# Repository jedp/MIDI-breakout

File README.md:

# MIDI Breakout Board

MIDI IN/OUT. 3V3 logic.

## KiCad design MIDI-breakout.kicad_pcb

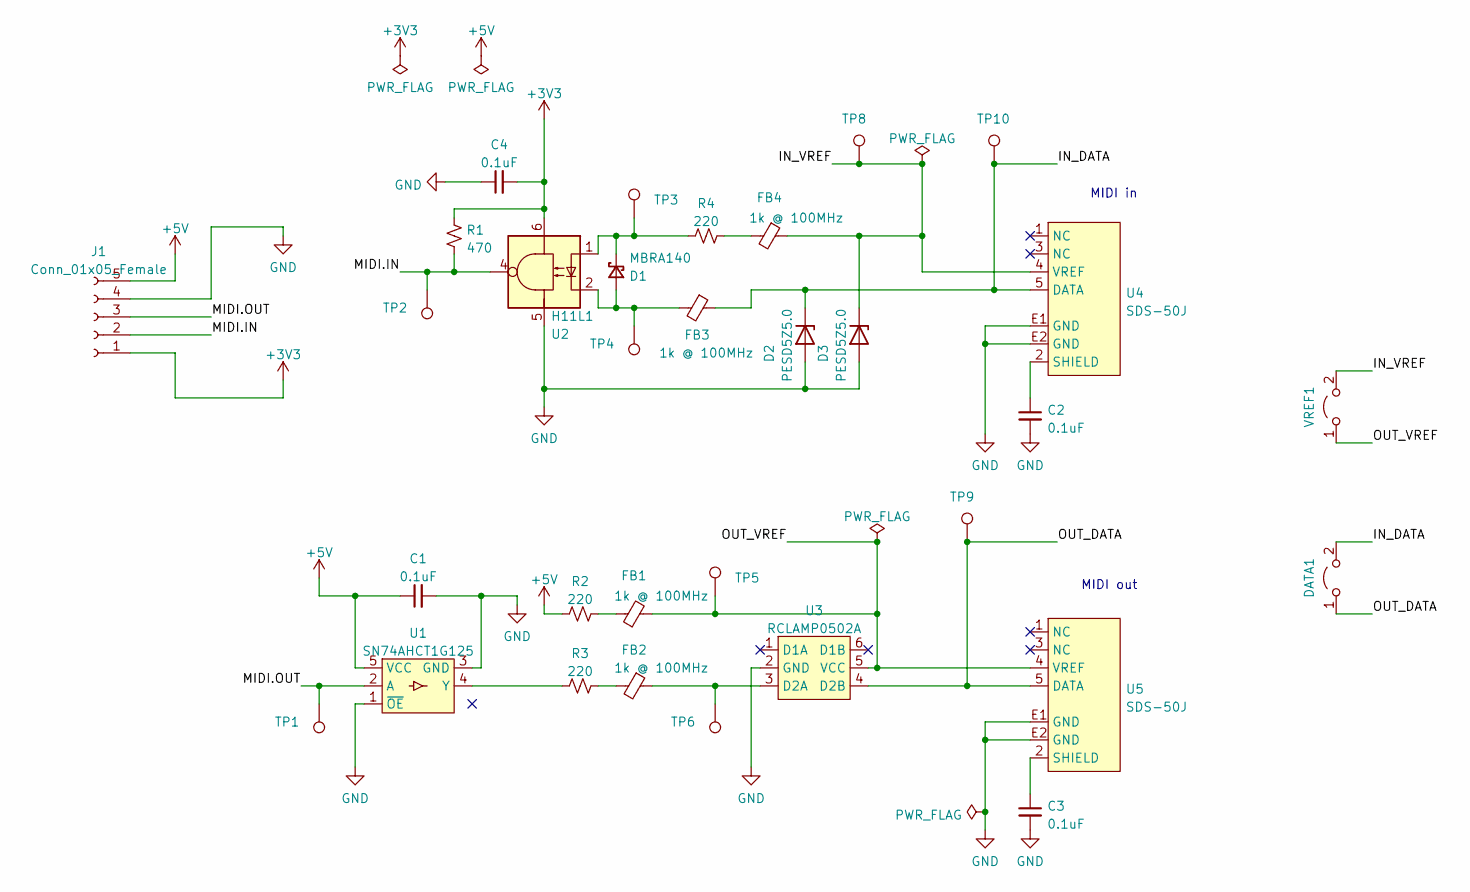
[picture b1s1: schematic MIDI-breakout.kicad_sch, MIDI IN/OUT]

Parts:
C1, C2, C3, C4: 0.1uF; C_0603_1608Metric
D1: MBRA140; DO-214AC (SMA)
D2, D3: PESD5Z5.0; D_SOD-523
DATA1: Jumper_2_Open; PinHeader_1x02_P2.54mm_Vertical
FB1, FB2, FB3, FB4: 1k @ 100MHz; L_0603_1608Metric
J1: Conn_01x05_Female; PinSocket_1x05_P2.54mm_Vertical
R1: 470; R_0603_1608Metric
R2, R3, R4: 220; R_0603_1608Metric
TP1, TP2, TP3, TP4, TP5, TP6, TP8, TP9, TP10: TestPoint; TestPoint_Pad_D1.0mm
U1: SN74AHCT1G125; SOT-23-5
U2: H11L1; DIP-6_W7.62mm
U3: RCLAMP0502A; SOT-666
U4, U5: SDS-50J; SDS-J
VREF1: Jumper_2_Open; PinHeader_1x02_P2.54mm_Vertical

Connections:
+3V3: C4.2, J1.1, R1.1, U2.6
+5V: C1.1, J1.5, R2.1, U1.5 (VCC)
/IN_DATA: D2.1 (K), DATA1.2 (B), FB3.1, TP10.1, U4.5 (DATA)
/IN_VREF: D3.1 (K), FB4.1, TP8.1, U4.4 (VREF), VREF1.2 (B)
/MIDI.IN: J1.2, R1.2, TP2.1, U2.4
/MIDI.OUT: J1.3, TP1.1, U1.2 (A)
/OUT_DATA: DATA1.1 (A), TP9.1, U3.4 (D2B), U5.5 (DATA)
/OUT_VREF: FB1.2, TP5.1, U3.5 (VCC), U5.4 (VREF), VREF1.1 (A)
GND: C1.2, C2.2, C3.2, C4.1, D2.2 (A), D3.2 (A), J1.4, U1.1 (~OE), U1.3 (GND), U2.5, U3.2 (GND), U4.E1 (GND), U4.E2 (GND), U5.E1 (GND), U5.E2 (GND)
unnamed: C2.1, U4.2 (SHIELD)
unnamed: C3.1, U5.2 (SHIELD)
unnamed: D1.1 (K), R4.1, TP3.1, U2.1
unnamed: D1.2 (A), FB3.2, TP4.1, U2.2
unnamed: FB1.1, R2.2
unnamed: FB2.1, TP6.1, U3.3 (D2A)
unnamed: FB2.2, R3.2
unnamed: FB4.2, R4.2
unnamed: R3.1, U1.4 (Y)

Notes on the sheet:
MIDI in
MIDI out

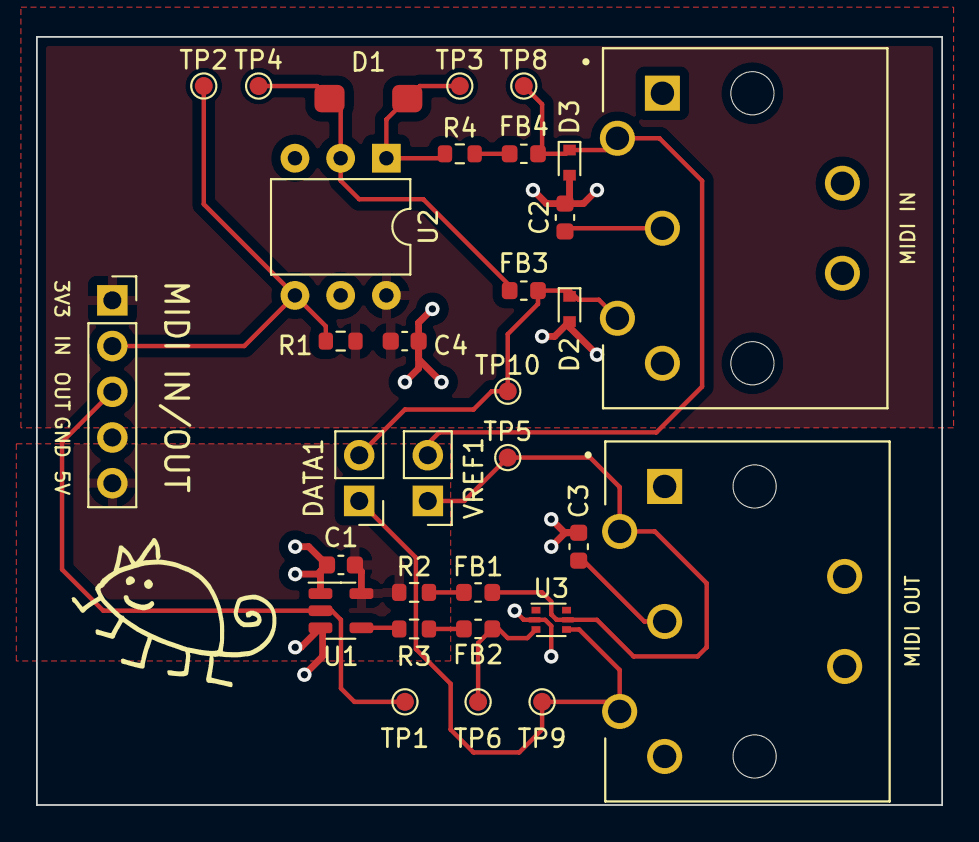
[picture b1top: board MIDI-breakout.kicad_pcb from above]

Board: 2 copper layers, 50.3 x 42.7 mm, 32 parts (0 on the bottom side), 18 nets.

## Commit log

2023-12-26 MIDI breakout board
2023-12-26 PCB image
